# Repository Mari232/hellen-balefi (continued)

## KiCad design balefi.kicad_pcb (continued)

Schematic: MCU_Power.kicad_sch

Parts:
C93, C96, C97, C100, C101, C102, C104: 10uF; C_1206_3216Metric; MPN CL31A106KBHNNNE
C94, C95, C98, C99, C103, C105: 100nF; C_0402_1005Metric; MPN CL05B104KB54PNC
D28: LED; LED_0603_1608Metric; MPN 150060AS75000
D29: V3P6HM3_A/H; Vishay_SMPA; MPN V3P6HM3_A/H
F6, F7: 350 mA; Fuse_1206_3216Metric; MPN 0ZCJ0035FF2G
FB1: 600 ohm 500mA; R_0603_1608Metric; MPN BLM18AG601SN1D
Q12, Q14: DMG2307LQ-7; SOT-23-3; MPN DMG2307LQ-7
Q13, Q15: RUC002N05HZGT116; SOT-23; MPN RUC002N05HZGT116
R142, R143, R144, R145, R146: 10k; R_0402_1005Metric; MPN AC0402JR-0710KL
U13: REF3033; SOT-23; MPN REF3033AIDBZR
U14: NCV1117DT33T5G; TO-252-2; MPN NCV1117DT33T5G

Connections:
/3V3: C104.1, F7.2; also elsewhere on the board
/5V: C93.1, C94.2, C97.1, C98.2, D29.1 (K), Q12.3 (S), R143.2, U13.1 (IN), U14.3 (VI); also elsewhere on the board
/5VA: C102.1, F6.2; also elsewhere on the board
/MCU_module/3V3: C99.2, C100.1, D28.2 (A), FB1.1, Q14.3 (S), R145.2, U14.2 (VO); also elsewhere on the board
/MCU_module/V33A: C101.1, FB1.2; also elsewhere on the board
/MCU_module/V33REF: C95.2, C96.1, U13.2 (OUT); also elsewhere on the board
/MCU_module/VBUS: D29.2 (A); also elsewhere on the board
/PWR_EN: Q13.1 (G), Q15.1 (G), R144.2, R146.2; also elsewhere on the board
GND: C93.2, C94.1, C95.1, C96.2, C97.2, C98.1, C99.1, C100.2, C101.2, C102.2, C103.1, C104.2, C105.1, Q13.3 (S), Q15.3 (S), R142.2, R144.1, R146.1, U13.3 (GND), U14.1 (GND); also elsewhere on the board
unnamed: D28.1 (K), R142.1
unnamed: C103.2, F6.1, Q12.2 (D)
unnamed: Q12.1 (G), Q13.2 (D), R143.1
unnamed: C105.2, F7.1, Q14.2 (D)
unnamed: Q14.1 (G), Q15.2 (D), R145.1

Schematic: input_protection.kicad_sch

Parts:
C72, C73, C74, C75: 10nF; C_0402_1005Metric; MPN GCM155R71H103MA55D
D23: NUP4202W1T2G; SOT-363_SC-70-6; MPN NUP4202W1T2G
R92, R93, R94, R95, R100, R101, R102, R103: 680k; R_0402_1005Metric; MPN WR06X6803FTL
R96, R97, R98, R99: 4k7; R_0402_1005Metric; MPN AC0402FR-074K7L

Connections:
/5VA: D23.5, R92.2, R93.2, R94.2, R95.2; also elsewhere on the board
/MCU_module/input_protection_1/OUT1: C72.1, D23.6, R96.2; also elsewhere on the board
/MCU_module/input_protection_1/OUT2: C73.1, D23.4, R97.2; also elsewhere on the board
/MCU_module/input_protection_1/OUT3: C74.1, D23.1, R98.2; also elsewhere on the board
/MCU_module/input_protection_1/OUT4: C75.1, D23.3, R99.2; also elsewhere on the board
/PPS1_IN: R94.1, R98.1, R102.2; also elsewhere on the board
/PPS2_IN: R95.1, R99.1, R103.2; also elsewhere on the board
/TPS1: R92.1, R96.1, R100.2; also elsewhere on the board
/TPS2: R93.1, R97.1, R101.2; also elsewhere on the board
GND: C72.2, C73.2, C74.2, C75.2, D23.2, R100.1, R101.1, R102.1, R103.1; also elsewhere on the board

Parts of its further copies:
C68, C69, C70, C71, C76, C77, C78, C79: 10nF; C_0402_1005Metric; MPN GCM155R71H103MA55D
D22, D24: NUP4202W1T2G; SOT-363_SC-70-6; MPN NUP4202W1T2G
R80, R81, R82, R83, R88, R89, R90, R91, R104, R105, R106, R107, R112, R113, R114, R115: 680k; R_0402_1005Metric; MPN WR06X6803FTL
R84, R85, R86, R87, R108, R109, R110, R111: 4k7; R_0402_1005Metric; MPN AC0402FR-074K7L

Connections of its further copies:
/5VA: D22.5, D24.5, R80.2, R81.2, R82.2, R83.2, R104.2, R105.2, R106.2, R107.2; also elsewhere on the board
/CAM_UC: R105.1, R109.1, R113.2; also elsewhere on the board
/CLT: R81.1, R85.1, R89.2; also elsewhere on the board
/CRANK_UC: R104.1, R108.1, R112.2; also elsewhere on the board
/IAT: R80.1, R84.1, R88.2; also elsewhere on the board
/KNOCK_UC: R107.1, R111.1, R115.2; also elsewhere on the board
/MAP: R82.1, R86.1, R90.2; also elsewhere on the board
/MCU_module/input_protection_2/OUT1: C68.1, D22.6, R84.2; also elsewhere on the board
/MCU_module/input_protection_2/OUT2: C69.1, D22.4, R85.2; also elsewhere on the board
/MCU_module/input_protection_2/OUT3: C70.1, D22.1, R86.2; also elsewhere on the board
/MCU_module/input_protection_2/OUT4: C71.1, D22.3, R87.2; also elsewhere on the board
/MCU_module/input_protection_3/OUT1: C76.1, D24.6, R108.2; also elsewhere on the board
/MCU_module/input_protection_3/OUT2: C77.1, D24.4, R109.2; also elsewhere on the board
/MCU_module/input_protection_3/OUT3: C78.1, D24.1, R110.2; also elsewhere on the board
/MCU_module/input_protection_3/OUT4: C79.1, D24.3, R111.2; also elsewhere on the board
/VMAIN_UC: R83.1, R87.1, R91.2; also elsewhere on the board
/VSS_UC: R106.1, R110.1, R114.2; also elsewhere on the board
GND: C68.2, C69.2, C70.2, C71.2, C76.2, C77.2, C78.2, C79.2, D22.2, D24.2, R88.1, R89.1, R90.1, R91.1, R112.1, R113.1, R114.1, R115.1; also elsewhere on the board

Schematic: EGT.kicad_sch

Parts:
C107: 1uF; C_0805_2012Metric; MPN CL21B105KBFNNNG
C108: 100nF; C_0402_1005Metric; MPN CL05B104KB54PNC
C109: 10nF; C_0402_1005Metric; MPN GCM155R71H103MA55D
D31: SZNUP2105L; SOT-23; MPN SZNUP2105LT1G
L3, L4: BLM18SP102SN1D; L_0603_1608Metric_Pad1.05x0.95mm_HandSolder
R153: 22; R_0402_1005Metric; MPN AC0402FR-0722RL
U16: MAX31855KASA; SOIC-8_3.9x4.9mm_P1.27mm

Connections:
/EGT+: D31.2 (K), L3.2; also elsewhere on the board
/EGT-: D31.1 (K), L4.2; also elsewhere on the board
/MCU_module/SPI3_CS: U16.6 (~CS); also elsewhere on the board
/MCU_module/SPI3_MISO: R153.1; also elsewhere on the board
/MCU_module/SPI3_SCK: U16.5 (SCK); also elsewhere on the board
/MCU_module/V33A: C107.1, C108.2, U16.4 (V_CC); also elsewhere on the board
GND: C107.2, C108.1, D31.3 (A), U16.1 (GND); also elsewhere on the board
unnamed: R153.2, U16.7 (SO)
unnamed: C109.2, L3.1, U16.3 (T+)
unnamed: C109.1, L4.1, U16.2 (T-)

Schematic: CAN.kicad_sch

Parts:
C65, C67: 100nF; C_0402_1005Metric; MPN CL05B104KB54PNC
C66: 4.7nF; C_0402_1005Metric; MPN GCM155R71H472KA37J
D21: SZNUP2105L; SOT-23; MPN SZNUP2105LT1G
R76, R79: 10; R_0402_1005Metric; MPN AC0402FR-0710RL
R77, R78: 60.4; R_0805_2012Metric; MPN AC0805FR-0760R4L
U10: TJA1051T/3/2Z; SOIC-8_3.9x4.9mm_P1.27mm; MPN TJA1051T/3/2Z

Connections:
/5V: C65.1, U10.3 (VCC); also elsewhere on the board
/CANH: D21.1 (K), R76.2, R77.1; also elsewhere on the board
/CANL: D21.2 (K), R78.2, R79.2; also elsewhere on the board
/MCU_module/3V3: C67.1, U10.5 (VIO); also elsewhere on the board
/MCU_module/CAN_RX: U10.4 (RXD); also elsewhere on the board
/MCU_module/CAN_TX: U10.1 (TXD); also elsewhere on the board
GND: C65.2, C66.2, C67.2, D21.3 (A), U10.2 (GND), U10.8 (S); also elsewhere on the board
unnamed: C66.1, R77.2, R78.1
unnamed: R76.1, U10.7 (CANH)
unnamed: R79.1, U10.6 (CANL)

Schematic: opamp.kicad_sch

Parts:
C60: 100nF; C_0402_1005Metric; MPN CL05B104KB54PNC
C61, C62, C63, C64: 390pF; C_0402_1005Metric; MPN GCM155R71H391KA37D
R68, R69, R70, R71, R72, R73, R74, R75: 2k7; R_0402_1005Metric; MPN AC0402FR-072K7L
U9: TLV9064; TSSOP-14_4.4x5mm_P0.65mm; MPN TLV9064QPWRQ1

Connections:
/5VA: C60.1, U9.4 (V+); also elsewhere on the board
/MCU_module/input_protection_1/OUT1: U9.3 (+); also elsewhere on the board
/MCU_module/input_protection_1/OUT2: U9.5 (+); also elsewhere on the board
/MCU_module/input_protection_1/OUT3: U9.10 (+); also elsewhere on the board
/MCU_module/input_protection_1/OUT4: U9.12 (+); also elsewhere on the board
/PPS1_IN: C63.1, R72.2, R73.2; also elsewhere on the board
/PPS2_IN: C64.1, R74.2, R75.2; also elsewhere on the board
/TPS1: C61.1, R68.2, R69.2; also elsewhere on the board
/TPS2: C62.1, R70.2, R71.2; also elsewhere on the board
GND: C60.2, C61.2, C62.2, C63.2, C64.2, R69.1, R71.1, R73.1, R75.1, U9.11 (V-); also elsewhere on the board
unnamed: R68.1, U9.1, U9.2 (-)
unnamed: R70.1, U9.6 (-), U9.7
unnamed: R72.1, U9.8, U9.9 (-)
unnamed: R74.1, U9.13 (-), U9.14

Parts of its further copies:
C32, C37: 100nF; C_0402_1005Metric; MPN CL05B104KB54PNC
C33, C34, C35, C36, C38, C39, C40, C41: 390pF; C_0402_1005Metric; MPN GCM155R71H391KA37D
R36, R37, R38, R39, R40, R41, R42, R43, R44, R45, R46, R47, R48, R49, R50, R51: 2k7; R_0402_1005Metric; MPN AC0402FR-072K7L
U5, U6: TLV9064; TSSOP-14_4.4x5mm_P0.65mm; MPN TLV9064QPWRQ1

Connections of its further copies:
/5VA: C32.1, C37.1, U5.4 (V+), U6.4 (V+); also elsewhere on the board
/CAM_UC: C39.1, R46.2, R47.2; also elsewhere on the board
/CLT: C34.1, R38.2, R39.2; also elsewhere on the board
/CRANK_UC: C38.1, R44.2, R45.2; also elsewhere on the board
/IAT: C33.1, R36.2, R37.2; also elsewhere on the board
/MAP: C35.1, R40.2, R41.2; also elsewhere on the board
/MCU_module/KNOCK: C41.1, R50.2, R51.2; also elsewhere on the board
/MCU_module/input_protection_2/OUT1: U5.3 (+); also elsewhere on the board
/MCU_module/input_protection_2/OUT2: U5.5 (+); also elsewhere on the board
/MCU_module/input_protection_2/OUT3: U5.10 (+); also elsewhere on the board
/MCU_module/input_protection_2/OUT4: U5.12 (+); also elsewhere on the board
/MCU_module/input_protection_3/OUT1: U6.3 (+); also elsewhere on the board
/MCU_module/input_protection_3/OUT2: U6.5 (+); also elsewhere on the board
/MCU_module/input_protection_3/OUT3: U6.10 (+); also elsewhere on the board
/MCU_module/input_protection_3/OUT4: U6.12 (+); also elsewhere on the board
/VMAIN_UC: C36.1, R42.2, R43.2; also elsewhere on the board
/VSS_UC: C40.1, R48.2, R49.2; also elsewhere on the board
GND: C32.2, C33.2, C34.2, C35.2, C36.2, C37.2, C38.2, C39.2, C40.2, C41.2, R37.1, R39.1, R41.1, R43.1, R45.1, R47.1, R49.1, R51.1, U5.11 (V-), U6.11 (V-); also elsewhere on the board
unnamed: R36.1, U5.1, U5.2 (-)
unnamed: R38.1, U5.6 (-), U5.7
unnamed: R40.1, U5.8, U5.9 (-)
unnamed: R42.1, U5.13 (-), U5.14
unnamed: R44.1, U6.1, U6.2 (-)
unnamed: R46.1, U6.6 (-), U6.7
unnamed: R48.1, U6.8, U6.9 (-)
unnamed: R50.1, U6.13 (-), U6.14

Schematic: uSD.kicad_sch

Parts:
C91: 10uF; C_1206_3216Metric; MPN CL31A106KBHNNNE
C92: 100nF; C_0402_1005Metric; MPN CL05B104KB54PNC
J4: MEM2067-02-180-00-A; MPN MEM2067-02-180-00-A
R140: 10k; R_0402_1005Metric; MPN AC0402JR-0710KL
R141: 1R; R_0603_1608Metric; MPN AF0603FR-071RL
R152: 22; R_0402_1005Metric; MPN AC0402FR-0722RL

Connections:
/MCU_module/3V3: R141.1; also elsewhere on the board
/MCU_module/SPI1_CS1: J4.2 (CD/DAT3), R140.1; also elsewhere on the board
/MCU_module/SPI1_MISO: J4.7 (DAT0), R152.1, R152.2; also elsewhere on the board
/MCU_module/SPI1_MOSI: J4.3 (CMD); also elsewhere on the board
/MCU_module/SPI1_SCK: J4.5 (CLK); also elsewhere on the board
GND: C91.2, C92.2, J4.6 (VSS), J4.TAB_1, J4.TAB_2, J4.TAB_3, J4.TAB_4; also elsewhere on the board
unnamed: C91.1, C92.1, J4.4 (VDD), R140.2, R141.2

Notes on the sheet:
MEM2067-02-180-00-A

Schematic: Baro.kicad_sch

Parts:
C106: 100nF; C_0402_1005Metric; MPN CL05B104KB54PNC
U15: LPS25HB; ST_HLGA-10_2.5x2.5mm_P0.6mm_LayoutBorder3x2y

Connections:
/MCU_module/3V3: C106.1, U15.1 (Vdd_IO), U15.6 (~CS), U15.10 (VDD); also elsewhere on the board
/MCU_module/I2C_SCL: U15.2 (SCL); also elsewhere on the board
/MCU_module/I2C_SDA: U15.4 (SDA); also elsewhere on the board
GND: C106.2, U15.3 (GND), U15.5 (SA0), U15.8 (GND), U15.9 (GND); also elsewhere on the board

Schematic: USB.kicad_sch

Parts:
D30: PRTR5V0U2X; SOT-143; MPN PRTR5V0U2AX,215
J5: Conn_01x06_Pin; JST_PH_B6B-PH-K_1x06_P2.00mm_Vertical; MPN B6B-PH-K-S
R147, R148: 5k1; R_0603_1608Metric

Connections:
/MCU_module/D+: D30.3 (I/O2), J5.2; also elsewhere on the board
/MCU_module/D-: D30.2 (I/O1), J5.3; also elsewhere on the board
/MCU_module/USB/CC1: J5.5, R147.1
/MCU_module/USB/CC2: J5.4, R148.1
/MCU_module/VBUS: D30.4 (VCC), J5.6; also elsewhere on the board
GND: D30.1 (GND), J5.1, R147.2, R148.2; also elsewhere on the board

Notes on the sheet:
Add USB ESD protection and CMC

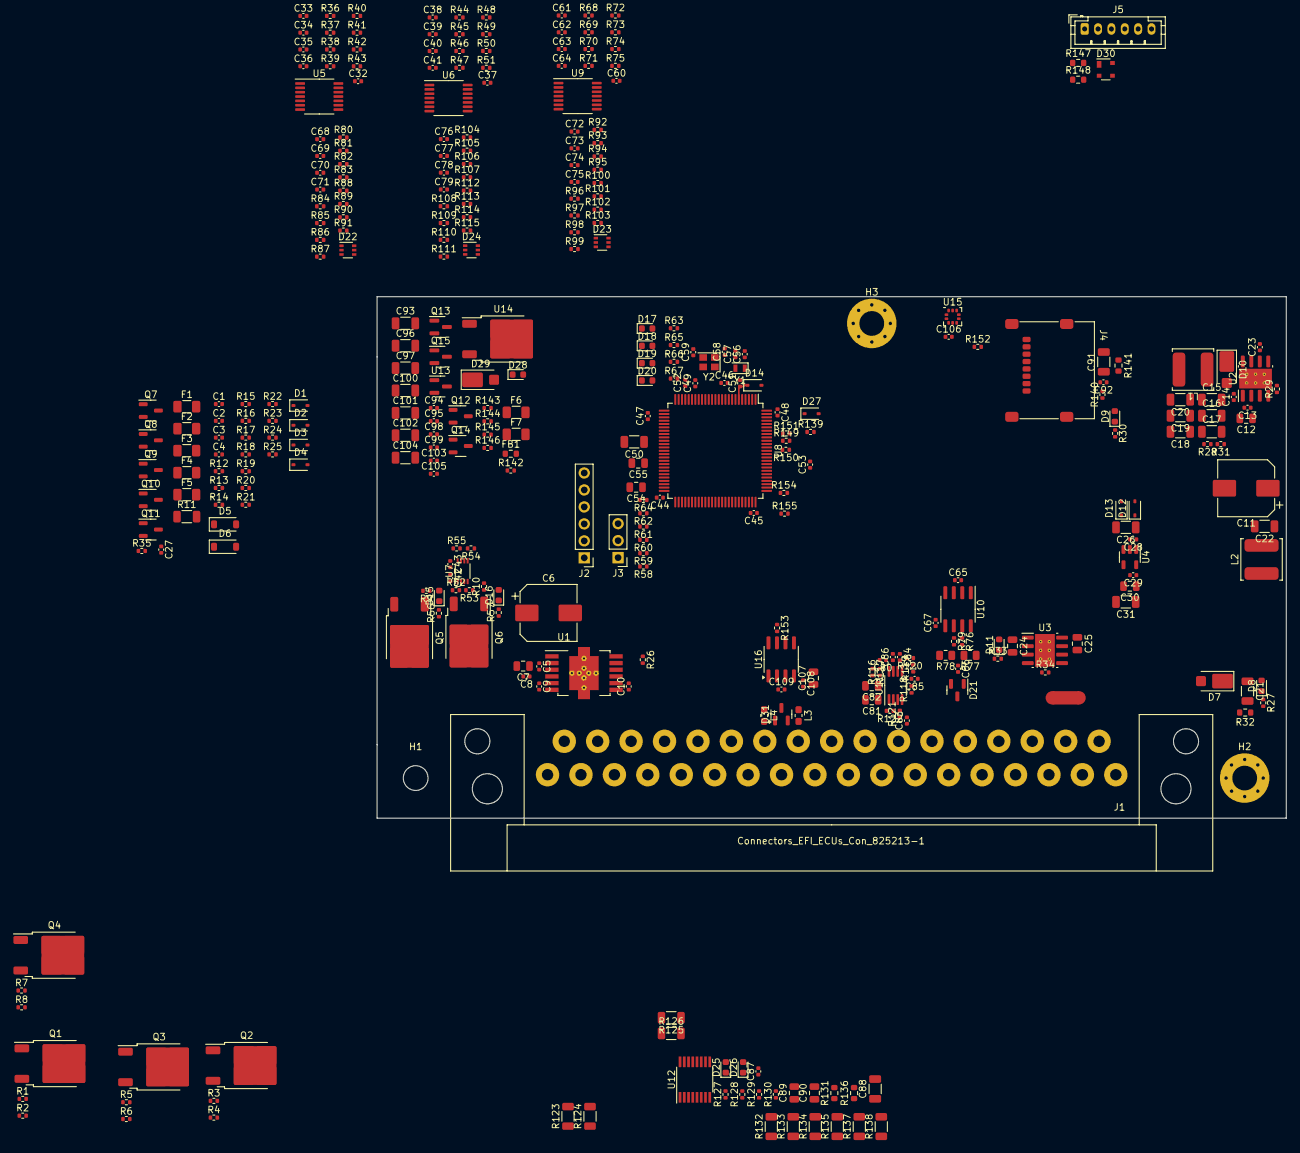
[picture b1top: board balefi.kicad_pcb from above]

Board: 4 copper layers, 136.0 x 78.0 mm, 349 parts (0 on the bottom side), 204 nets.

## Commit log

2024-02-28 Added submodule kicad-libraries
2024-02-28 First PCB design commit
2024-02-28 Change file names
2024-02-28 Added outer dimmensions for PCB, added origin point
2024-02-28 [skip actions] Auto-generated board v2.1
2024-03-05 Started designing schematic
2024-06-03 a lot of changes
